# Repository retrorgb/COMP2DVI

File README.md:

# COMP2DVI
Please refer to the [COMP2DVI](https://www.retrorgb.com/comp2dvi.html) page on RetroRGB for more information.

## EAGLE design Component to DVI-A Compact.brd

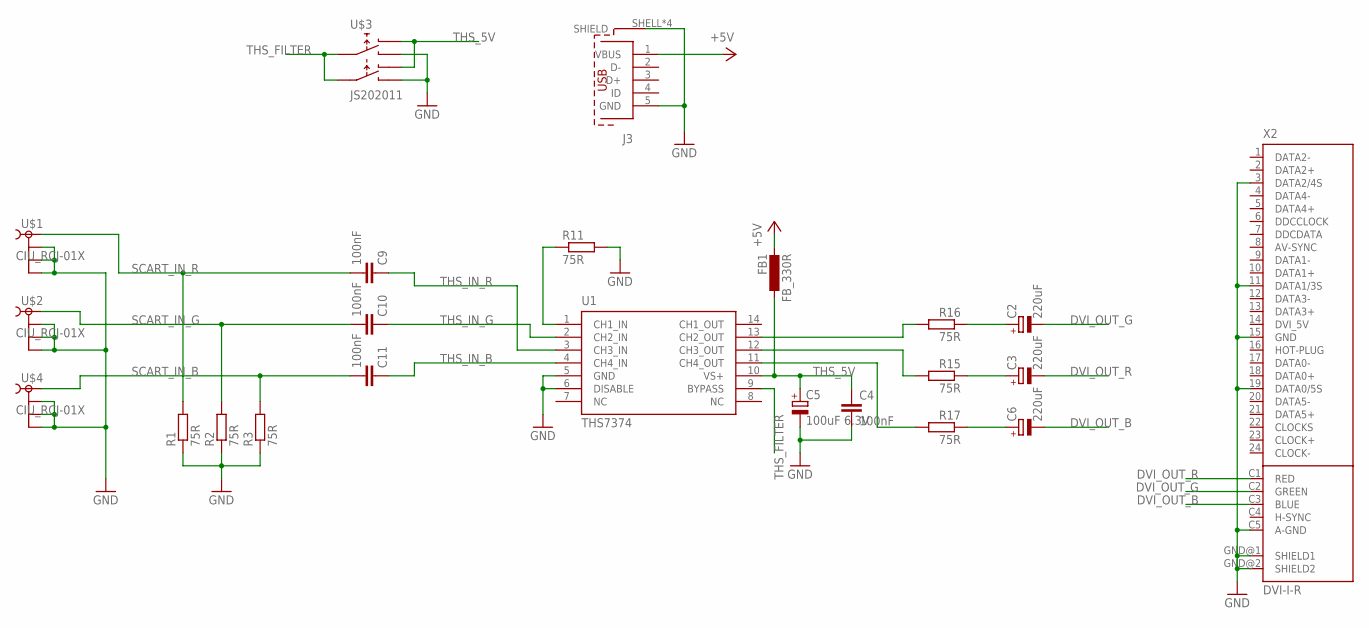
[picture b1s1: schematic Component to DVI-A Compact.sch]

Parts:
C2, C3, C6: 220uF; SMC_C
C4, C9, C10, C11: 100nF; C0603
C5: 100uF 6.3V; PANASONIC_B
FB1: FB_330R; L2012C
J3: 629105150521
R1, R2, R3, R11, R15, R16, R17: 75R; R0603
U1: THS7374; SO14W
U$1, U$2, U$4: CIU_RCJ-01X
U$3: JS202011
X2: DVI-I-R

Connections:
+5V: FB1.2, J3.1 (VBUS)
AGND: X2.C6 (AGND)
CH1_OUT: R15.2, U1.12 (CH3_OUT)
CH2_OUT: R16.2, U1.13 (CH2_OUT)
CH3_OUT: R17.2, U1.11 (CH4_OUT)
DVI_5V: X2.14 (DVI_5V)
DVI_OUT_B: C6.-, X2.C3 (BLUE)
DVI_OUT_G: C2.-, X2.C2 (GREEN)
DVI_OUT_R: C3.-, X2.C1 (RED)
GND: C4.2, C5.-, J3.5 (GND), J3.SHELL (SHIELD), J3.SHELL1 (SHIELD), J3.SHELL2 (SHIELD), J3.SHELL3 (SHIELD), R1.1, R2.1, R3.1, R11.2, U1.5 (GND), U1.6 (DISABLE), U$1.2@1 (2), U$1.2@2 (3), U$1.2@3 (4), U$2.2@1 (2), U$2.2@2 (3), U$2.2@3 (4), U$3.1, U$3.4, U$4.2@1 (2), U$4.2@2 (3), U$4.2@3 (4), X2.3 (DATA2/4S), X2.11 (DATA1/3S), X2.15 (GND), X2.19 (DATA0/5S), X2.C5 (A-GND), X2.GND@1 (SHIELD1), X2.GND@2 (SHIELD2)
unnamed: C6.+, R17.1
unnamed: C3.+, R15.1
unnamed: C2.+, R16.1
unnamed: R11.1, U1.1 (CH1_IN)
SCART_IN_B: C11.2, R3.2, U$4.1
SCART_IN_G: C10.2, R2.2, U$2.1
SCART_IN_R: C9.2, R1.2, U$1.1
THS_5V: C4.1, C5.+, FB1.1, U1.10 (VS+), U$3.3, U$3.6
THS_FILTER: U1.9 (BYPASS), U$3.2, U$3.5
THS_IN_B: C11.1, U1.4 (CH4_IN)
THS_IN_G: C10.1, U1.2 (CH2_IN)
THS_IN_R: C9.1, U1.3 (CH3_IN)

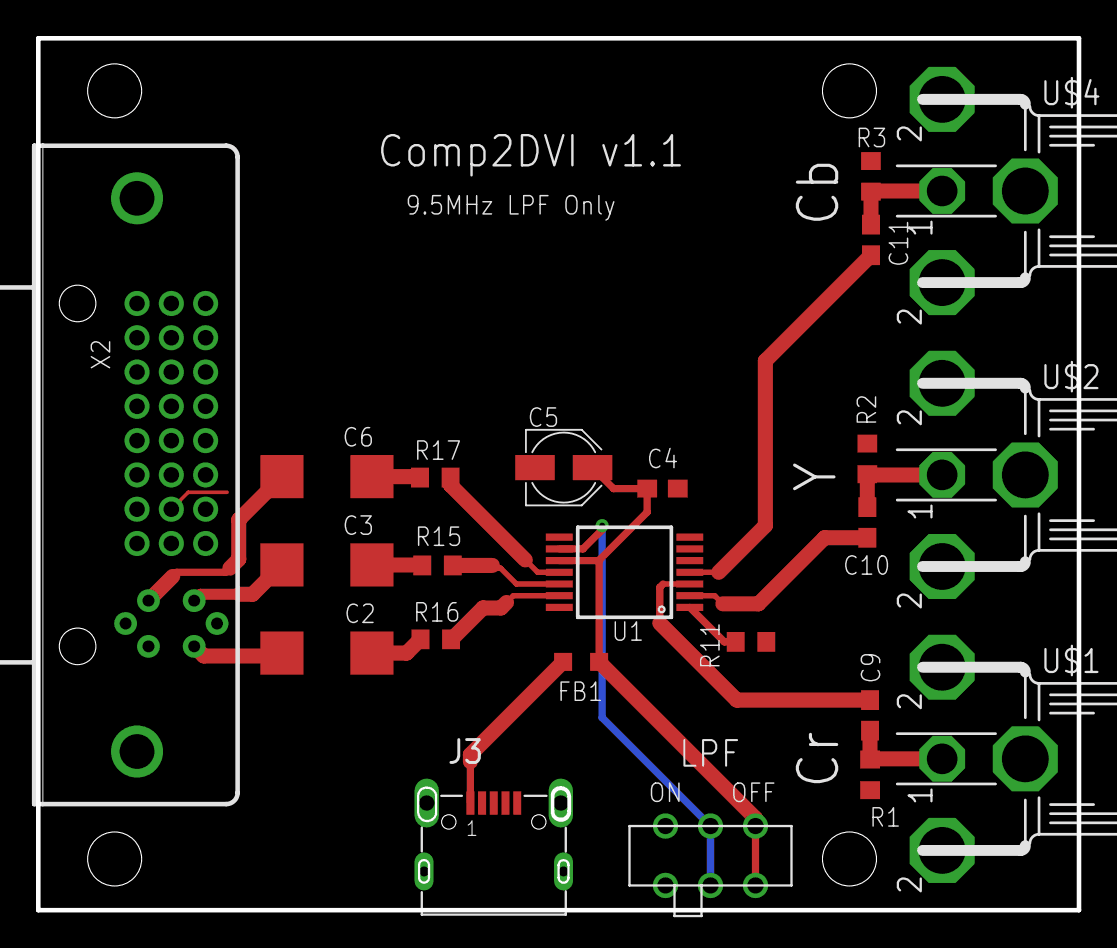
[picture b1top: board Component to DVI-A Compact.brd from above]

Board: 2 copper layers, 57.8 x 48.4 mm, 23 parts (0 on the bottom side), 20 nets.

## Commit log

2019-06-13 Initial Eagle Version
    Initial Eagle version of the Comp2DVI
2019-06-13 Converted to KiCAD
2019-06-13 2.1 version
    Changed to THS7368 amp. This involced adding a dip switch and selector switch to determine the bandwidth of the video filter. Changed micro-usb port to a more commonly available part.
2019-06-13 Create license
2019-06-13 Added README
2019-06-17 Bypass Cap Routing
    Fixed routing so that the power from the USB goes to the 100nF bypass cap before hitting the chip. Thanks to Tianfeng for pointing this out. Gerbers updated as well.
2019-06-17 renamed gerber zip
2019-06-26 Fixed overlapping silkscreen
    Fixed overlap, won't change version number or make a new release for this.
2019-08-18 Updated BOM
    BOM now matches current version and includes case hardware.
2019-10-24 removed old files

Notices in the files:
parts and their libraries:
con-wurth: Copyright: Würth Elektronik
